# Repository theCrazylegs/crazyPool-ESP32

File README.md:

# crazyPool-ESP32
 
Piscine connectée IOT

SONDES : Température / Ph / Consommation électrique

Prérequis : 
* 1 ESP32 
* 1 Kit Sonde Ph https://www.dfrobot.com/product-1782.html 
* 1 Kit Sonde Température : https://www.dfrobot.com/product-1354.html 
* 3 boutons poussoirs 
* 1 Potentiomètre 10K 
* 1 PZEM004T 
* 1 écran LCD 16x2 
* 1 porte Sonde pour le PH 
* 1 Doigt de gant (1/2 pouce puits thermique) pour la sonde de Température 
* 1 Sonde de PH plus robuste que la sonde de labo fournis par dfrobot qui n'aurait pas tenu la pression dans les tuyaux 
* 2 Presse-étoupes 
* 24 AWG 0,2mm² Kit de Fil électrique 
* 1 carte PCB Prototype 70mmx90mm 
* 1 Boitier (158 * 90 * 60mm) 
* 2 Connecteurs pour Blindage arduino (pour connecter l'ESP32) 
* x Connecteurs JST

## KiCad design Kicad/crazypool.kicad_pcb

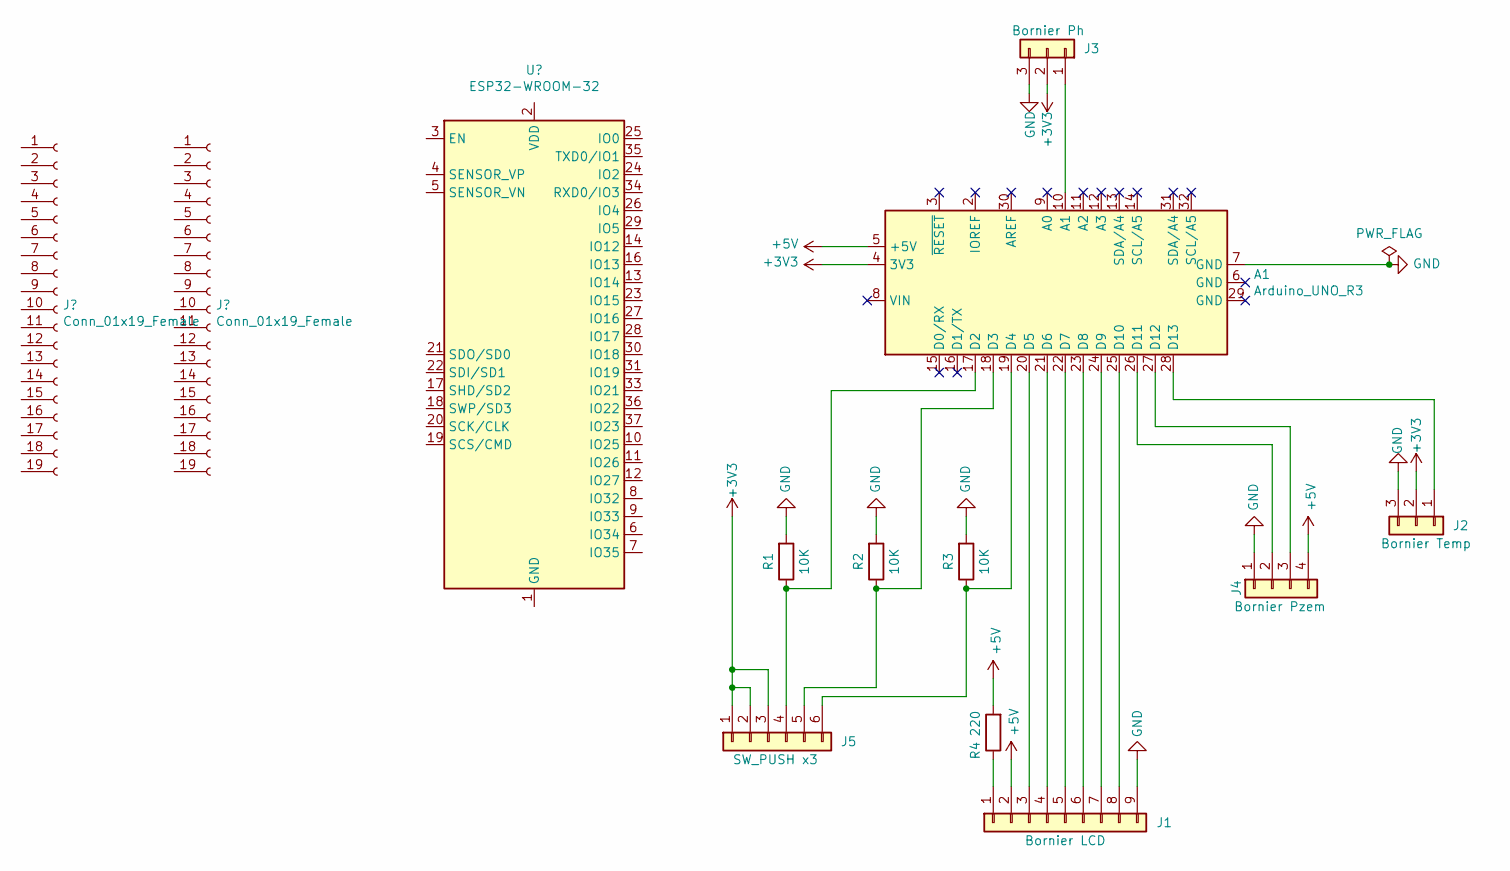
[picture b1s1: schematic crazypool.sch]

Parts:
A1: Arduino_UNO_R3
J1: Bornier LCD; JST_PH_B9B-PH-K_1x09_P2.00mm_Vertical
J2: Bornier Temp; JST_PH_B3B-PH-K_1x03_P2.00mm_Vertical
J3: Bornier Ph; JST_PH_B3B-PH-K_1x03_P2.00mm_Vertical
J4: Bornier Pzem; JST_PH_B4B-PH-K_1x04_P2.00mm_Vertical
J5: SW_PUSH x3; JST_PH_B6B-PH-K_1x06_P2.00mm_Vertical
R1, R2, R3: 10K; R_Axial_DIN0204_L3.6mm_D1.6mm_P7.62mm_Horizontal
R4: 220; R_Axial_DIN0204_L3.6mm_D1.6mm_P7.62mm_Horizontal

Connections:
+3V3: A1.4 (3V3), J2.2, J3.2, J5.1, J5.2, J5.3
+5V: A1.5 (+5V), J1.2, J4.4, R4.2
GND: A1.7 (GND), J1.9, J2.3, J3.3, J4.1, R1.2, R2.2, R3.2
unnamed: A1.10 (A1), J3.1
unnamed: A1.17 (D2), J5.4, R1.1
unnamed: A1.18 (D3), J5.5, R2.1
unnamed: A1.19 (D4), J5.6, R3.1
unnamed: A1.20 (D5), J1.3
unnamed: A1.21 (D6), J1.4
unnamed: A1.22 (D7), J1.5
unnamed: A1.23 (D8), J1.6
unnamed: A1.24 (D9), J1.7
unnamed: A1.25 (D10), J1.8
unnamed: A1.26 (D11), J4.2
unnamed: A1.27 (D12), J4.3
unnamed: A1.28 (D13), J2.1
unnamed: J1.1, R4.1

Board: 2 copper layers, 9 parts (0 on the bottom side), 7 nets, no tracks yet.
